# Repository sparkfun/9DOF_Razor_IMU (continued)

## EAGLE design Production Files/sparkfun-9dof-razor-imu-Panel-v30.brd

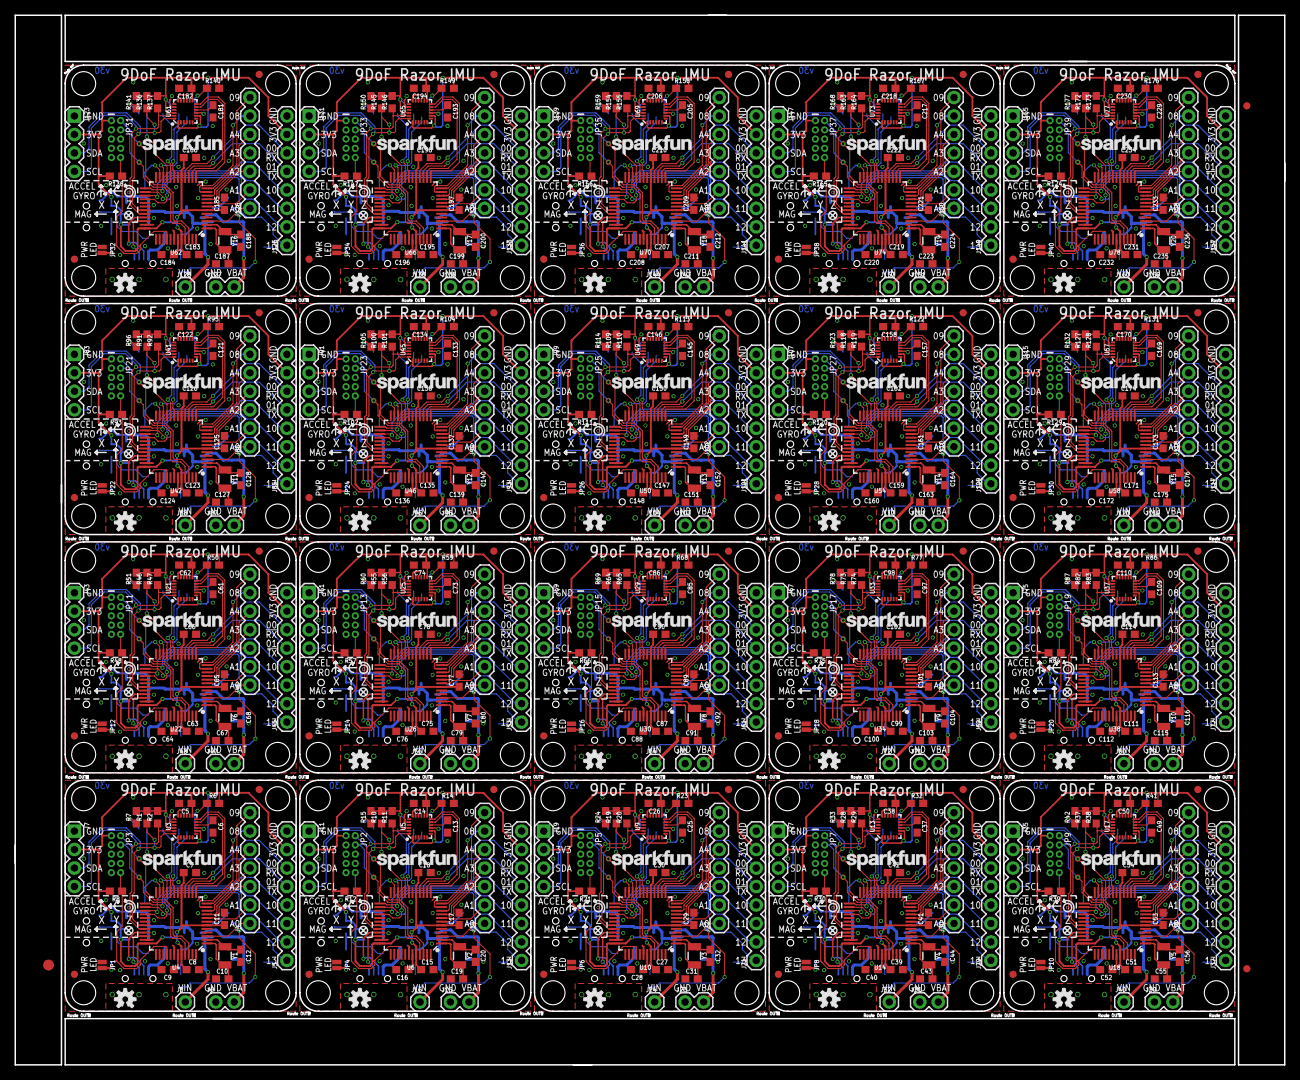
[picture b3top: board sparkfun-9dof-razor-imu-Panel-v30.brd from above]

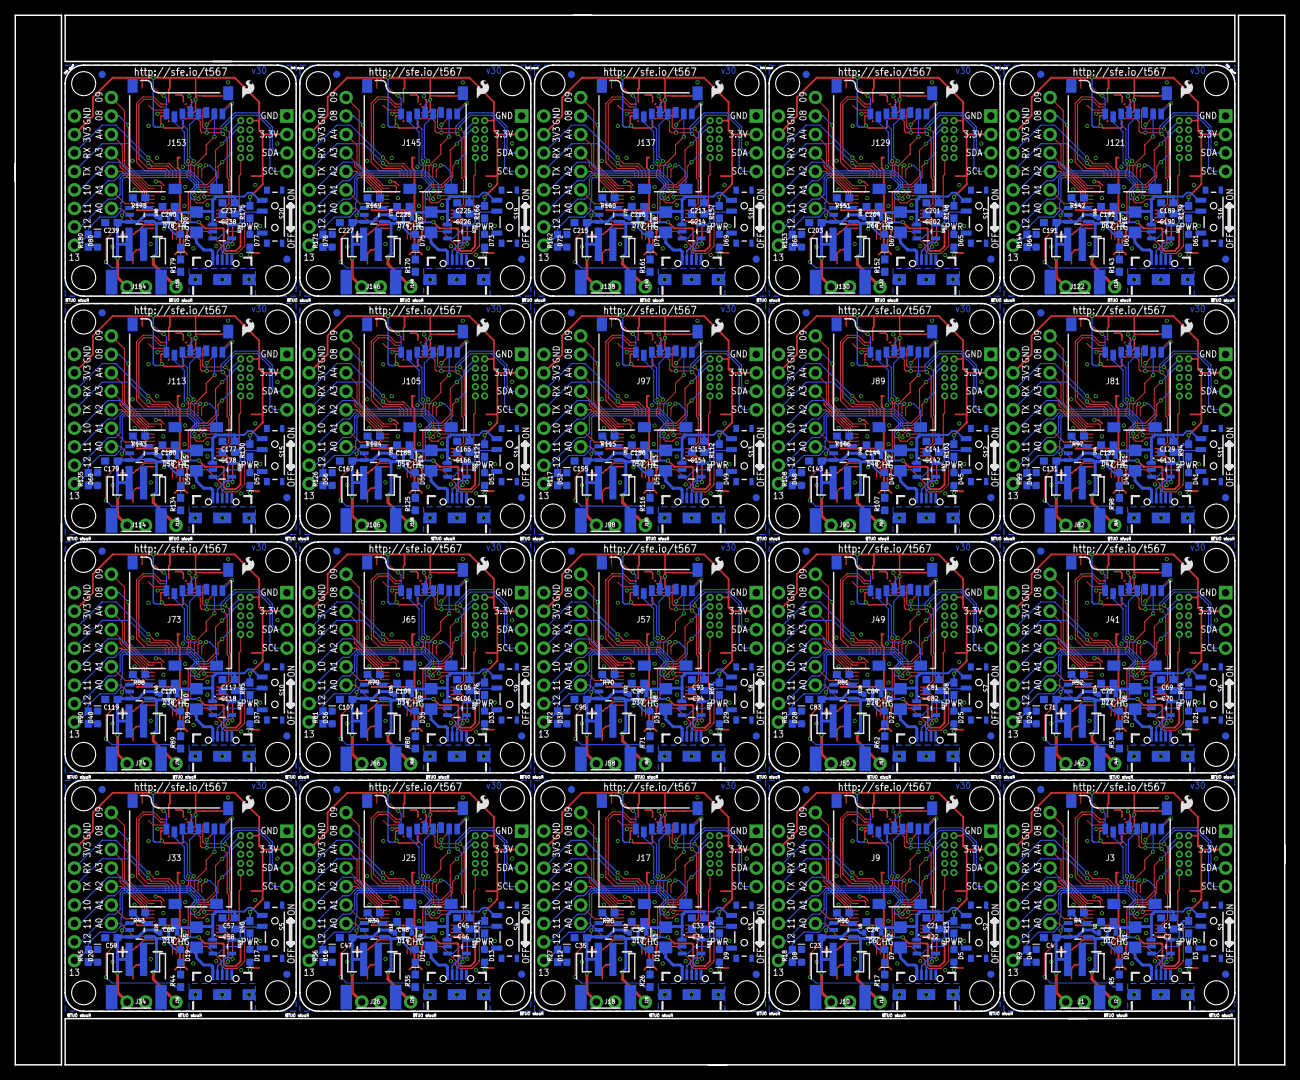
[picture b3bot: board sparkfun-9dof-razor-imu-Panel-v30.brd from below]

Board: 2 copper layers, 174.5 x 144.3 mm, 1103 parts (440 on the bottom side), 920 nets.

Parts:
C1, C21, C33, C45, C57, C69, C81, C93, C105, C117, C129, C141, C153, C165, C177, C189, C201, C213, C225, C237: 1.0uF; 0603
C2, C22, C34, C46, C58, C70, C82, C94, C106, C118, C130, C142, C154, C166, C178, C190, C202, C214, C226, C238: 2.2uF; 0603
C3, C4, C23, C24, C35, C36, C47, C48, C59, C60, C71, C72, C83, C84, C95, C96, C107, C108, C119, C120, C131, C132, C143, C144, C155, C156, C167, C168, C179, C180, C191, C192, C203, C204, C215, C216, C227, C228, C239, C240: 4.7uF; 0603
C5, C6, C7, C8, C9, C11, C13, C14, C15, C16, C17, C18, C25, C26, C27, C28, C29, C30, C37, C38, C39, C40, C41, C42, C49, C50, C51, C52, C53, C54, C61, C62, C63, C64, C65, C66, C73, C74, C75, C76, C77, C78, C85, C86, C87, C88, C89, C90, C97, C98, C99, C100, C101, C102, C109, C110, C111, C112, C113, C114, C121, C122, C123, C124, C125, C126, C133, C134, C135, C136, C137, C138, C145, C146, C147, C148, C149, C150, C157, C158, C159, C160, C161, C162, C169, C170, C171, C172, C173, C174, C181, C182, C183, C184, C185, C186, C193, C194, C195, C196, C197, C198, C205, C206, C207, C208, C209, C210, C217, C218, C219, C220, C221, C222, C229, C230, C231, C232, C233, C234: 0.1uF; 0603
C10, C12, C19, C20, C31, C32, C43, C44, C55, C56, C67, C68, C79, C80, C91, C92, C103, C104, C115, C116, C127, C128, C139, C140, C151, C152, C163, C164, C175, C176, C187, C188, C199, C200, C211, C212, C223, C224, C235, C236: 15pF; 0603
D1, D6, D10, D14, D18, D22, D26, D30, D34, D38, D42, D46, D50, D54, D58, D62, D66, D70, D74, D78: 1A/23V/620mV; SOD-323
D2, D7, D11, D15, D19, D23, D27, D31, D35, D39, D43, D47, D51, D55, D59, D63, D67, D71, D75, D79: Yellow; LED-0603
D3, D5, D9, D13, D17, D21, D25, D29, D33, D37, D41, D45, D49, D53, D57, D61, D65, D69, D73, D77: RED; LED-0603
D4, D8, D12, D16, D20, D24, D28, D32, D36, D40, D44, D48, D52, D56, D60, D64, D68, D72, D76, D80: BLUE; LED-0603
E$1: FIDUCIAL-1.5X3
E$7, E$8: FIDUCIAL-1X2
F1, F2, F3, F4, F5, F6, F7, F8, F9, F10, F11, F12, F13, F14, F15, F16, F17, F18, F19, F20: 6V/0.5A; 1206
FD1, FD2, FD3, FD4, FD5, FD6, FD7, FD8, FD9, FD10, FD11, FD12, FD13, FD14, FD15, FD16, FD17, FD18, FD19, FD20, FD21, FD22, FD23, FD24, FD25, FD26, FD27, FD28, FD29, FD30, FD31, FD32, FD33, FD34, FD35, FD36, FD37, FD38, FD39, FD40, FD41, FD42, FD43, FD44, FD45, FD46, FD47, FD48, FD49, FD50, FD51, FD52, FD53, FD54, FD55, FD56, FD57, FD58, FD59, FD60, FD61, FD62, FD63, FD64, FD65, FD66, FD67, FD68, FD69, FD70, FD71, FD72, FD73, FD74, FD75, FD76, FD77, FD78, FD79, FD80: FIDUCIAL1X2; FIDUCIAL-1X2
H1, H2, H3, H4, H5, H6, H7, H8, H9, H10, H11, H12, H13, H14, H15, H16, H17, H18, H19, H20, H21, H22, H23, H24, H25, H26, H27, H28, H29, H30, H31, H32, H33, H34, H35, H36, H37, H38, H39, H40, H41, H42, H43, H44, H45, H46, H47, H48, H49, H50, H51, H52, H53, H54, H55, H56, H57, H58, H59, H60, H61, H62, H63, H64, H65, H66, H67, H68, H69, H70, H71, H72, H73, H74, H75, H76, H77, H78, H79, H80: STAND-OFF
J1, J10, J18, J26, J34, J42, J50, J58, J66, J74, J82, J90, J98, J106, J114, J122, J130, J138, J146, J154: LiPo; JST-2-SMD
J2, J12, J20, J28, J36, J44, J52, J60, J68, J76, J84, J92, J100, J108, J116, J124, J132, J140, J148, J156: USB-B-MICRO-SMD_V03
J3, J9, J17, J25, J33, J41, J49, J57, J65, J73, J81, J89, J97, J105, J113, J121, J129, J137, J145, J153: USD_CONNECTOR; MICRO-SD-SOCKET-PP
J4, J14, J22, J30, J38, J46, J54, J62, J70, J78, J86, J94, J102, J110, J118, J126, J134, J142, J150, J158: 1X07
J5, J13, J21, J29, J37, J45, J53, J61, J69, J77, J85, J93, J101, J109, J117, J125, J133, J141, J149, J157: 1X08
J6, J15, J23, J31, J39, J47, J55, J63, J71, J79, J87, J95, J103, J111, J119, J127, J135, J143, J151, J159: 1X02
J7, J11, J19, J27, J35, J43, J51, J59, J67, J75, J83, J91, J99, J107, J115, J123, J131, J139, J147, J155: 1X04
J8, J16, J24, J32, J40, J48, J56, J64, J72, J80, J88, J96, J104, J112, J120, J128, J136, J144, J152, J160: 1X01
JP1, JP4, JP6, JP8, JP10, JP12, JP14, JP16, JP18, JP20, JP22, JP24, JP26, JP28, JP30, JP32, JP34, JP36, JP38, JP40: LED; SMT-JUMPER_2_NC_PASTE_NO-SILK
JP2, JP3, JP5, JP7, JP9, JP11, JP13, JP15, JP17, JP19, JP21, JP23, JP25, JP27, JP29, JP31, JP33, JP35, JP37, JP39: CORTEX_DEBUGPTH; 2X5-PTH-1.27MM
LOGO1, LOGO4, LOGO7, LOGO10, LOGO13, LOGO16, LOGO19, LOGO22, LOGO25, LOGO28, LOGO31, LOGO34, LOGO37, LOGO40, LOGO43, LOGO46, LOGO49, LOGO52, LOGO55, LOGO58: SFE_LOGO_FLAME.1_INCH; SFE_LOGO_FLAME_.1
LOGO2, LOGO5, LOGO8, LOGO11, LOGO14, LOGO17, LOGO20, LOGO23, LOGO26, LOGO29, LOGO32, LOGO35, LOGO38, LOGO41, LOGO44, LOGO47, LOGO50, LOGO53, LOGO56, LOGO59: OSHW-LOGOS; OSHW-LOGO-S
LOGO3, LOGO6, LOGO9, LOGO12, LOGO15, LOGO18, LOGO21, LOGO24, LOGO27, LOGO30, LOGO33, LOGO36, LOGO39, LOGO42, LOGO45, LOGO48, LOGO51, LOGO54, LOGO57, LOGO60: SFE_LOGO_NAME.1_INCH; SFE_LOGO_NAME_.1
R1, R2, R10, R11, R19, R20, R28, R29, R37, R38, R46, R47, R55, R56, R64, R65, R73, R74, R82, R83, R91, R92, R100, R101, R109, R110, R118, R119, R127, R128, R136, R137, R145, R146, R154, R155, R163, R164, R172, R173: 4.7k; 0603
R3, R5, R9, R13, R17, R18, R22, R26, R27, R31, R35, R36, R40, R44, R45, R49, R53, R54, R58, R62, R63, R67, R71, R72, R76, R80, R81, R85, R89, R90, R94, R98, R99, R103, R107, R108, R112, R116, R117, R121, R125, R126, R130, R134, R135, R139, R143, R144, R148, R152, R153, R157, R161, R162, R166, R170, R171, R175, R179, R180: 1k; 0603
R4, R16, R25, R34, R43, R52, R61, R70, R79, R88, R97, R106, R115, R124, R133, R142, R151, R160, R169, R178: 2.2k; 0603
R6, R7, R14, R15, R23, R24, R32, R33, R41, R42, R50, R51, R59, R60, R68, R69, R77, R78, R86, R87, R95, R96, R104, R105, R113, R114, R122, R123, R131, R132, R140, R141, R149, R150, R158, R159, R167, R168, R176, R177: 100k; 0603
R8, R12, R21, R30, R39, R48, R57, R66, R75, R84, R93, R102, R111, R120, R129, R138, R147, R156, R165, R174: 10k; 0603
S1, S2, S3, S4, S5, S6, S7, S8, S9, S10, S11, S12, S13, S14, S15, S16, S17, S18, S19, S20: SWITCH-SPST-SMD-A
TP1, TP2, TP3, TP4, TP5, TP6, TP7, TP8, TP9, TP10, TP11, TP12, TP13, TP14, TP15, TP16, TP17, TP18, TP19, TP20, TP21, TP22, TP23, TP24, TP25, TP26, TP27, TP28, TP29, TP30, TP31, TP32, TP33, TP34, TP35, TP36, TP37, TP38, TP39, TP40: TEST-POINT3; PAD.03X.03
U1, U7, U11, U15, U19, U23, U27, U31, U35, U39, U43, U47, U51, U55, U59, U63, U67, U71, U75, U79: 3.3V; SOT23-5
U2, U8, U12, U16, U20, U24, U28, U32, U36, U40, U44, U48, U52, U56, U60, U64, U68, U72, U76, U80: MCP73831; SOT23-5
U3, U5, U9, U13, U17, U21, U25, U29, U33, U37, U41, U45, U49, U53, U57, U61, U65, U69, U73, U77: MPU-9250; QFN24-3X3
U4, U6, U10, U14, U18, U22, U26, U30, U34, U38, U42, U46, U50, U54, U58, U62, U66, U70, U74, U78: ATSAMD21G-A; TQFP-48
Y1, Y2, Y3, Y4, Y5, Y6, Y7, Y8, Y9, Y10, Y11, Y12, Y13, Y14, Y15, Y16, Y17, Y18, Y19, Y20: 32.768kHz; CRYSTAL-SMD-3.2X1.5MM

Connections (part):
3.3V: C2.1, C5.1, C7.1, C8.1, C11.1, J3.VCC, J5.7, J7.2, JP3.1, R1.2, R2.2, R3.2, R6.2, R7.2, R8.2, U1.5, U3.1, U3.8, U3.13, U3.22, U4.6, U4.17, U4.36, U4.44
3.3V1: C14.1, C15.1, C17.1, C18.1, C22.1, J9.VCC, J11.2, J13.7, JP2.1, R10.2, R11.2, R12.2, R13.2, R14.2, R15.2, U5.1, U5.8, U5.13, U5.22, U6.6, U6.17, U6.36, U6.44, U7.5
3.3V2: C26.1, C27.1, C29.1, C30.1, C34.1, J17.VCC, J19.2, J21.7, JP5.1, R19.2, R20.2, R21.2, R22.2, R23.2, R24.2, U9.1, U9.8, U9.13, U9.22, U10.6, U10.17, U10.36, U10.44, U11.5
3.3V3: C38.1, C39.1, C41.1, C42.1, C46.1, J25.VCC, J27.2, J29.7, JP7.1, R28.2, R29.2, R30.2, R31.2, R32.2, R33.2, U13.1, U13.8, U13.13, U13.22, U14.6, U14.17, U14.36, U14.44, U15.5
3.3V4: C50.1, C51.1, C53.1, C54.1, C58.1, J33.VCC, J35.2, J37.7, JP9.1, R37.2, R38.2, R39.2, R40.2, R41.2, R42.2, U17.1, U17.8, U17.13, U17.22, U18.6, U18.17, U18.36, U18.44, U19.5
3.3V5: C62.1, C63.1, C65.1, C66.1, C70.1, J41.VCC, J43.2, J45.7, JP11.1, R46.2, R47.2, R48.2, R49.2, R50.2, R51.2, U21.1, U21.8, U21.13, U21.22, U22.6, U22.17, U22.36, U22.44, U23.5
3.3V6: C74.1, C75.1, C77.1, C78.1, C82.1, J49.VCC, J51.2, J53.7, JP13.1, R55.2, R56.2, R57.2, R58.2, R59.2, R60.2, U25.1, U25.8, U25.13, U25.22, U26.6, U26.17, U26.36, U26.44, U27.5
3.3V7: C86.1, C87.1, C89.1, C90.1, C94.1, J57.VCC, J59.2, J61.7, JP15.1, R64.2, R65.2, R66.2, R67.2, R68.2, R69.2, U29.1, U29.8, U29.13, U29.22, U30.6, U30.17, U30.36, U30.44, U31.5
3.3V8: C98.1, C99.1, C101.1, C102.1, C106.1, J65.VCC, J67.2, J69.7, JP17.1, R73.2, R74.2, R75.2, R76.2, R77.2, R78.2, U33.1, U33.8, U33.13, U33.22, U34.6, U34.17, U34.36, U34.44, U35.5
3.3V9: C110.1, C111.1, C113.1, C114.1, C118.1, J73.VCC, J75.2, J77.7, JP19.1, R82.2, R83.2, R84.2, R85.2, R86.2, R87.2, U37.1, U37.8, U37.13, U37.22, U38.6, U38.17, U38.36, U38.44, U39.5
3.3V10: C122.1, C123.1, C125.1, C126.1, C130.1, J81.VCC, J83.2, J85.7, JP21.1, R91.2, R92.2, R93.2, R94.2, R95.2, R96.2, U41.1, U41.8, U41.13, U41.22, U42.6, U42.17, U42.36, U42.44, U43.5
3.3V11: C134.1, C135.1, C137.1, C138.1, C142.1, J89.VCC, J91.2, J93.7, JP23.1, R100.2, R101.2, R102.2, R103.2, R104.2, R105.2, U45.1, U45.8, U45.13, U45.22, U46.6, U46.17, U46.36, U46.44, U47.5
3.3V12: C146.1, C147.1, C149.1, C150.1, C154.1, J97.VCC, J99.2, J101.7, JP25.1, R109.2, R110.2, R111.2, R112.2, R113.2, R114.2, U49.1, U49.8, U49.13, U49.22, U50.6, U50.17, U50.36, U50.44, U51.5
3.3V13: C158.1, C159.1, C161.1, C162.1, C166.1, J105.VCC, J107.2, J109.7, JP27.1, R118.2, R119.2, R120.2, R121.2, R122.2, R123.2, U53.1, U53.8, U53.13, U53.22, U54.6, U54.17, U54.36, U54.44, U55.5
3.3V14: C170.1, C171.1, C173.1, C174.1, C178.1, J113.VCC, J115.2, J117.7, JP29.1, R127.2, R128.2, R129.2, R130.2, R131.2, R132.2, U57.1, U57.8, U57.13, U57.22, U58.6, U58.17, U58.36, U58.44, U59.5
3.3V15: C182.1, C183.1, C185.1, C186.1, C190.1, J121.VCC, J123.2, J125.7, JP31.1, R136.2, R137.2, R138.2, R139.2, R140.2, R141.2, U61.1, U61.8, U61.13, U61.22, U62.6, U62.17, U62.36, U62.44, U63.5
3.3V16: C194.1, C195.1, C197.1, C198.1, C202.1, J129.VCC, J131.2, J133.7, JP33.1, R145.2, R146.2, R147.2, R148.2, R149.2, R150.2, U65.1, U65.8, U65.13, U65.22, U66.6, U66.17, U66.36, U66.44, U67.5
3.3V17: C206.1, C207.1, C209.1, C210.1, C214.1, J137.VCC, J139.2, J141.7, JP35.1, R154.2, R155.2, R156.2, R157.2, R158.2, R159.2, U69.1, U69.8, U69.13, U69.22, U70.6, U70.17, U70.36, U70.44, U71.5
3.3V18: C218.1, C219.1, C221.1, C222.1, C226.1, J145.VCC, J147.2, J149.7, JP37.1, R163.2, R164.2, R165.2, R166.2, R167.2, R168.2, U73.1, U73.8, U73.13, U73.22, U74.6, U74.17, U74.36, U74.44, U75.5
3.3V19: C230.1, C231.1, C233.1, C234.1, C238.1, J153.VCC, J155.2, J157.7, JP39.1, R172.2, R173.2, R174.2, R175.2, R176.2, R177.2, U77.1, U77.8, U77.13, U77.22, U78.6, U78.17, U78.36, U78.44, U79.5
!RESET: JP3.10, R8.1, U4.40
!RESET1: JP2.10, R12.1, U6.40
!RESET2: JP5.10, R21.1, U10.40
!RESET3: JP7.10, R30.1, U14.40
!RESET4: JP9.10, R39.1, U18.40
!RESET5: JP11.10, R48.1, U22.40
!RESET6: JP13.10, R57.1, U26.40
!RESET7: JP15.10, R66.1, U30.40
!RESET8: JP17.10, R75.1, U34.40
!RESET9: JP19.10, R84.1, U38.40
!RESET10: JP21.10, R93.1, U42.40
!RESET11: JP23.10, R102.1, U46.40
!RESET12: JP25.10, R111.1, U50.40
!RESET13: JP27.10, R120.1, U54.40
!RESET14: JP29.10, R129.1, U58.40
!RESET15: JP31.10, R138.1, U62.40
!RESET16: JP33.10, R147.1, U66.40
!RESET17: JP35.10, R156.1, U70.40
!RESET18: JP37.10, R165.1, U74.40
!RESET19: JP39.10, R174.1, U78.40
A0: J4.1, U4.3
A1: J4.2, U4.7
A2: J4.3, U4.8
A3: J4.4, U4.9
A4: J4.5, U4.10
A6: J14.2, U6.7
A7: J14.1, U6.3
A8: J14.3, U6.8
A9: J14.4, U6.9
A10: J14.5, U6.10
A12: J22.2, U10.7
A13: J22.1, U10.3
A14: J22.3, U10.8
A15: J22.4, U10.9
A16: J22.5, U10.10
A18: J30.2, U14.7
A19: J30.1, U14.3
A20: J30.3, U14.8
A21: J30.4, U14.9
A22: J30.5, U14.10
A24: J38.2, U18.7
A25: J38.1, U18.3
A26: J38.3, U18.8
A27: J38.4, U18.9
A28: J38.5, U18.10
A30: J46.2, U22.7
A31: J46.1, U22.3
A32: J46.3, U22.8
A33: J46.4, U22.9
A34: J46.5, U22.10
A36: J54.2, U26.7
A37: J54.1, U26.3
A38: J54.3, U26.8
A39: J54.4, U26.9
A40: J54.5, U26.10
A42: J62.2, U30.7
A43: J62.1, U30.3
A44: J62.3, U30.8
A45: J62.4, U30.9
A46: J62.5, U30.10
A48: J70.2, U34.7
A49: J70.1, U34.3
A50: J70.3, U34.8
A51: J70.4, U34.9
A52: J70.5, U34.10
A54: J78.2, U38.7
A55: J78.1, U38.3
A56: J78.3, U38.8
A57: J78.4, U38.9
A58: J78.5, U38.10
A60: J86.2, U42.7
A61: J86.1, U42.3
A62: J86.3, U42.8
A63: J86.4, U42.9
A64: J86.5, U42.10
A66: J94.2, U46.7
A67: J94.1, U46.3
A68: J94.3, U46.8
A69: J94.4, U46.9
A70: J94.5, U46.10
A72: J102.2, U50.7
A73: J102.1, U50.3
A74: J102.3, U50.8
A75: J102.4, U50.9
A76: J102.5, U50.10
A78: J110.2, U54.7
A79: J110.1, U54.3
A80: J110.3, U54.8
A81: J110.4, U54.9
A82: J110.5, U54.10
A84: J118.2, U58.7
A85: J118.1, U58.3
A86: J118.3, U58.8
A87: J118.4, U58.9
A88: J118.5, U58.10
A90: J126.2, U62.7
A91: J126.1, U62.3
A92: J126.3, U62.8
A93: J126.4, U62.9
A94: J126.5, U62.10
A96: J134.2, U66.7
A97: J134.1, U66.3
A98: J134.3, U66.8
A99: J134.4, U66.9
A100: J134.5, U66.10
A102: J142.2, U70.7
A103: J142.1, U70.3
A104: J142.3, U70.8
A105: J142.4, U70.9
A106: J142.5, U70.10
A108: J150.2, U74.7
A109: J150.1, U74.3
A110: J150.3, U74.8
A111: J150.4, U74.9
A112: J150.5, U74.10
A114: J158.2, U78.7
A115: J158.1, U78.3
A116: J158.3, U78.8
A117: J158.4, U78.9
A118: J158.5, U78.10
CHG_LED: R5.1, U2.1
CHG_LED1: R17.1, U8.1
CHG_LED2: R26.1, U12.1
CHG_LED3: R35.1, U16.1
CHG_LED4: R44.1, U20.1
CHG_LED5: R53.1, U24.1
CHG_LED6: R62.1, U28.1
CHG_LED7: R71.1, U32.1
CHG_LED8: R80.1, U36.1
CHG_LED9: R89.1, U40.1
CHG_LED10: R98.1, U44.1
CHG_LED11: R107.1, U48.1
CHG_LED12: R116.1, U52.1
CHG_LED13: R125.1, U56.1
CHG_LED14: R134.1, U60.1
CHG_LED15: R143.1, U64.1
CHG_LED16: R152.1, U68.1
CHG_LED17: R161.1, U72.1
CHG_LED18: R170.1, U76.1
CHG_LED19: R179.1, U80.1
D0/RXI: J5.6, U4.16
D0/RXI1: J13.6, U6.16
D0/RXI2: J21.6, U10.16
D0/RXI3: J29.6, U14.16
D0/RXI4: J37.6, U18.16
D0/RXI5: J45.6, U22.16
D0/RXI6: J53.6, U26.16
D0/RXI7: J61.6, U30.16
D0/RXI8: J69.6, U34.16
D0/RXI9: J77.6, U38.16
D0/RXI10: J85.6, U42.16
D0/RXI11: J93.6, U46.16
D0/RXI12: J101.6, U50.16
D0/RXI13: J109.6, U54.16
D0/RXI14: J117.6, U58.16
D0/RXI15: J125.6, U62.16
D0/RXI16: J133.6, U66.16
D0/RXI17: J141.6, U70.16
D0/RXI18: J149.6, U74.16
D0/RXI19: J157.6, U78.16
D1/TXO: J5.5, U4.15
D1/TXO1: J13.5, U6.15
D1/TXO2: J21.5, U10.15
D1/TXO3: J29.5, U14.15
D1/TXO4: J37.5, U18.15
D1/TXO5: J45.5, U22.15
D1/TXO6: J53.5, U26.15
D1/TXO7: J61.5, U30.15
D1/TXO8: J69.5, U34.15
D1/TXO9: J77.5, U38.15
D1/TXO10: J85.5, U42.15
D1/TXO11: J93.5, U46.15
D1/TXO12: J101.5, U50.15
D1/TXO13: J109.5, U54.15
D1/TXO14: J117.5, U58.15
D1/TXO15: J125.5, U62.15
D1/TXO16: J133.5, U66.15
D1/TXO17: J141.5, U70.15
D1/TXO18: J149.5, U74.15
D1/TXO19: J157.5, U78.15
D2/SD_CD: J3.CD1, U4.23
D2/SD_CD1: J9.CD1, U6.23
D2/SD_CD2: J17.CD1, U10.23
D2/SD_CD3: J25.CD1, U14.23
D2/SD_CD4: J33.CD1, U18.23
D2/SD_CD5: J41.CD1, U22.23
D2/SD_CD6: J49.CD1, U26.23
D2/SD_CD7: J57.CD1, U30.23
D2/SD_CD8: J65.CD1, U34.23
D2/SD_CD9: J73.CD1, U38.23
D2/SD_CD10: J81.CD1, U42.23
D2/SD_CD11: J89.CD1, U46.23
D2/SD_CD12: J97.CD1, U50.23
D2/SD_CD13: J105.CD1, U54.23
D2/SD_CD14: J113.CD1, U58.23
D2/SD_CD15: J121.CD1, U62.23
D2/SD_CD16: J129.CD1, U66.23
D2/SD_CD17: J137.CD1, U70.23
D2/SD_CD18: J145.CD1, U74.23
D2/SD_CD19: J153.CD1, U78.23
D3/FSYNC: U3.11, U4.14
D3/FSYNC1: U5.11, U6.14
D3/FSYNC2: U9.11, U10.14
D3/FSYNC3: U13.11, U14.14
D3/FSYNC4: U17.11, U18.14
D3/FSYNC5: U21.11, U22.14
D3/FSYNC6: U25.11, U26.14
D3/FSYNC7: U29.11, U30.14
D3/FSYNC8: U33.11, U34.14
D3/FSYNC9: U37.11, U38.14
D3/FSYNC10: U41.11, U42.14
D3/FSYNC11: U45.11, U46.14
D3/FSYNC12: U49.11, U50.14
D3/FSYNC13: U53.11, U54.14
D3/FSYNC14: U57.11, U58.14
D3/FSYNC15: U61.11, U62.14
D3/FSYNC16: U65.11, U66.14
D3/FSYNC17: U69.11, U70.14
D3/FSYNC18: U73.11, U74.14
D3/FSYNC19: U77.11, U78.14
D4: J13.2, U6.28
D4/INT: U3.12, U4.13
D4/INT1: U5.12, U6.13
D4/INT2: U9.12, U10.13
D4/INT3: U13.12, U14.13
D4/INT4: U17.12, U18.13
D4/INT5: U21.12, U22.13
D4/INT6: U25.12, U26.13
D4/INT7: U29.12, U30.13
D4/INT8: U33.12, U34.13
D4/INT9: U37.12, U38.13
D4/INT10: U41.12, U42.13
D4/INT11: U45.12, U46.13
D4/INT12: U49.12, U50.13
D4/INT13: U53.12, U54.13
D4/INT14: U57.12, U58.13
D4/INT15: U61.12, U62.13
D4/INT16: U65.12, U66.13
D4/INT17: U69.12, U70.13
D4/INT18: U73.12, U74.13
D4/INT19: U77.12, U78.13
D8: J4.6, U4.11
D9: J4.7, U4.12
D10: J5.4, U4.27
D11: J5.3, U4.25
D12: J5.2, U4.28
D13: J5.1, R9.2, U4.26
D14: J13.4, U6.27
D15: J13.3, U6.25
D16: J13.1, R18.2, U6.26
D17: J14.6, U6.11
D18: J14.7, U6.12
D22: J21.2, U10.28
D23: J21.4, U10.27
D24: J21.3, U10.25
D25: J21.1, R27.2, U10.26
D26: J22.6, U10.11
D27: J22.7, U10.12
D31: J29.2, U14.28
D32: J29.4, U14.27
D33: J29.3, U14.25
D34: J29.1, R36.2, U14.26
D35: J30.6, U14.11
D36: J30.7, U14.12
D40: J37.2, U18.28
D41: J37.4, U18.27
D42: J37.3, U18.25
D43: J37.1, R45.2, U18.26
D44: J38.6, U18.11
D45: J38.7, U18.12
D49: J45.2, U22.28
D50: J45.4, U22.27
D51: J45.3, U22.25
D52: J45.1, R54.2, U22.26
D53: J46.6, U22.11
D54: J46.7, U22.12
D58: J53.2, U26.28
D59: J53.4, U26.27
D60: J53.3, U26.25
D61: J53.1, R63.2, U26.26
D62: J54.6, U26.11
D63: J54.7, U26.12
D67: J61.2, U30.28
D68: J61.4, U30.27
D69: J61.3, U30.25
D70: J61.1, R72.2, U30.26
D71: J62.6, U30.11
D72: J62.7, U30.12
D76: J69.2, U34.28
D77: J69.4, U34.27
D78: J69.3, U34.25
D79: J69.1, R81.2, U34.26
D80: J70.6, U34.11
D81: J70.7, U34.12
D85: J77.2, U38.28
D86: J77.4, U38.27
D87: J77.3, U38.25
D88: J77.1, R90.2, U38.26
D89: J78.6, U38.11
D90: J78.7, U38.12
D94: J85.2, U42.28
D95: J85.4, U42.27
D96: J85.3, U42.25
D97: J85.1, R99.2, U42.26
D98: J86.6, U42.11
D99: J86.7, U42.12
D103: J93.2, U46.28
D104: J93.4, U46.27
D105: J93.3, U46.25
D106: J93.1, R108.2, U46.26
D107: J94.6, U46.11
D108: J94.7, U46.12
D112: J101.2, U50.28
D113: J101.4, U50.27
D114: J101.3, U50.25
D115: J101.1, R117.2, U50.26
D116: J102.6, U50.11
D117: J102.7, U50.12
D121: J109.2, U54.28
D122: J109.4, U54.27
D123: J109.3, U54.25
D124: J109.1, R126.2, U54.26
D125: J110.6, U54.11
D126: J110.7, U54.12
D130: J117.2, U58.28
D131: J117.4, U58.27
D132: J117.3, U58.25
D133: J117.1, R135.2, U58.26
D134: J118.6, U58.11
D135: J118.7, U58.12
D139: J125.2, U62.28
D140: J125.4, U62.27
D141: J125.3, U62.25
D142: J125.1, R144.2, U62.26
D143: J126.6, U62.11
D144: J126.7, U62.12
D148: J133.2, U66.28
D149: J133.4, U66.27
D150: J133.3, U66.25
D151: J133.1, R153.2, U66.26
D152: J134.6, U66.11
D153: J134.7, U66.12
D157: J141.2, U70.28
D158: J141.4, U70.27
D159: J141.3, U70.25
D160: J141.1, R162.2, U70.26
D161: J142.6, U70.11
D162: J142.7, U70.12
D166: J149.2, U74.28
D167: J149.4, U74.27
D168: J149.3, U74.25
D169: J149.1, R171.2, U74.26
D170: J150.6, U74.11
D171: J150.7, U74.12
D175: J157.2, U78.28
D176: J157.4, U78.27
D177: J157.3, U78.25
D178: J157.1, R180.2, U78.26
D179: J158.6, U78.11
D180: J158.7, U78.12
D+: J2.D+, U4.34
D+1: J12.D+, U6.34
D+2: J20.D+, U10.34
D+3: J28.D+, U14.34
D+4: J36.D+, U18.34
D+5: J44.D+, U22.34
D+6: J52.D+, U26.34
D+7: J60.D+, U30.34
D+8: J68.D+, U34.34
D+9: J76.D+, U38.34
D+10: J84.D+, U42.34
D+11: J92.D+, U46.34
D+12: J100.D+, U50.34
D+13: J108.D+, U54.34
D+14: J116.D+, U58.34
D+15: J124.D+, U62.34
D+16: J132.D+, U66.34
D+17: J140.D+, U70.34
D+18: J148.D+, U74.34
D+19: J156.D+, U78.34
D-: J2.D-, U4.33
D-1: J12.D-, U6.33
D-2: J20.D-, U10.33
D-3: J28.D-, U14.33
D-4: J36.D-, U18.33
D-5: J44.D-, U22.33
D-6: J52.D-, U26.33
D-7: J60.D-, U30.33
D-8: J68.D-, U34.33
D-9: J76.D-, U38.33
D-10: J84.D-, U42.33
D-11: J92.D-, U46.33
D-12: J100.D-, U50.33
D-13: J108.D-, U54.33
D-14: J116.D-, U58.33
D-15: J124.D-, U62.33
D-16: J132.D-, U66.33
D-17: J140.D-, U70.33
D-18: J148.D-, U74.33
D-19: J156.D-, U78.33
GND: C1.2, C2.2, C3.2, C4.2, C5.2, C6.2, C7.2, C8.2, C9.2, C10.1, C11.2, C12.2, D4.C, J1.1, J2.GND, J3.GND, J3.GND1, J3.GND3, J5.8, J6.1, J7.1, JP1.1, JP3.3, JP3.5, R4.1, S1.3, U1.2, U2.2, U3.9, U3.18, U3.20, U4.5, U4.18, U4.35, U4.42
GND1: C13.2, C14.2, C15.2, C16.2, C17.2, C18.2, C19.1, C20.2, C21.2, C22.2, C23.2, C24.2, D8.C, J9.GND, J9.GND1, J9.GND3, J10.1, J11.1, J12.GND, J13.8, J15.1, JP2.3, JP2.5, JP4.1, R16.1, S2.3, U5.9, U5.18, U5.20, U6.5, U6.18, U6.35, U6.42, U7.2, U8.2
GND2: C25.2, C26.2, C27.2, C28.2, C29.2, C30.2, C31.1, C32.2, C33.2, C34.2, C35.2, C36.2, D12.C, J17.GND, J17.GND1, J17.GND3, J18.1, J19.1, J20.GND, J21.8, J23.1, JP5.3, JP5.5, JP6.1, R25.1, S3.3, U9.9, U9.18, U9.20, U10.5, U10.18, U10.35, U10.42, U11.2, U12.2
GND3: C37.2, C38.2, C39.2, C40.2, C41.2, C42.2, C43.1, C44.2, C45.2, C46.2, C47.2, C48.2, D16.C, J25.GND, J25.GND1, J25.GND3, J26.1, J27.1, J28.GND, J29.8, J31.1, JP7.3, JP7.5, JP8.1, R34.1, S4.3, U13.9, U13.18, U13.20, U14.5, U14.18, U14.35, U14.42, U15.2, U16.2
GND4: C49.2, C50.2, C51.2, C52.2, C53.2, C54.2, C55.1, C56.2, C57.2, C58.2, C59.2, C60.2, D20.C, J33.GND, J33.GND1, J33.GND3, J34.1, J35.1, J36.GND, J37.8, J39.1, JP9.3, JP9.5, JP10.1, R43.1, S5.3, U17.9, U17.18, U17.20, U18.5, U18.18, U18.35, U18.42, U19.2, U20.2
GND5: C61.2, C62.2, C63.2, C64.2, C65.2, C66.2, C67.1, C68.2, C69.2, C70.2, C71.2, C72.2, D24.C, J41.GND, J41.GND1, J41.GND3, J42.1, J43.1, J44.GND, J45.8, J47.1, JP11.3, JP11.5, JP12.1, R52.1, S6.3, U21.9, U21.18, U21.20, U22.5, U22.18, U22.35, U22.42, U23.2, U24.2
GND6: C73.2, C74.2, C75.2, C76.2, C77.2, C78.2, C79.1, C80.2, C81.2, C82.2, C83.2, C84.2, D28.C, J49.GND, J49.GND1, J49.GND3, J50.1, J51.1, J52.GND, J53.8, J55.1, JP13.3, JP13.5, JP14.1, R61.1, S7.3, U25.9, U25.18, U25.20, U26.5, U26.18, U26.35, U26.42, U27.2, U28.2
GND7: C85.2, C86.2, C87.2, C88.2, C89.2, C90.2, C91.1, C92.2, C93.2, C94.2, C95.2, C96.2, D32.C, J57.GND, J57.GND1, J57.GND3, J58.1, J59.1, J60.GND, J61.8, J63.1, JP15.3, JP15.5, JP16.1, R70.1, S8.3, U29.9, U29.18, U29.20, U30.5, U30.18, U30.35, U30.42, U31.2, U32.2
GND8: C97.2, C98.2, C99.2, C100.2, C101.2, C102.2, C103.1, C104.2, C105.2, C106.2, C107.2, C108.2, D36.C, J65.GND, J65.GND1, J65.GND3, J66.1, J67.1, J68.GND, J69.8, J71.1, JP17.3, JP17.5, JP18.1, R79.1, S9.3, U33.9, U33.18, U33.20, U34.5, U34.18, U34.35, U34.42, U35.2, U36.2
GND9: C109.2, C110.2, C111.2, C112.2, C113.2, C114.2, C115.1, C116.2, C117.2, C118.2, C119.2, C120.2, D40.C, J73.GND, J73.GND1, J73.GND3, J74.1, J75.1, J76.GND, J77.8, J79.1, JP19.3, JP19.5, JP20.1, R88.1, S10.3, U37.9, U37.18, U37.20, U38.5, U38.18, U38.35, U38.42, U39.2, U40.2
GND10: C121.2, C122.2, C123.2, C124.2, C125.2, C126.2, C127.1, C128.2, C129.2, C130.2, C131.2, C132.2, D44.C, J81.GND, J81.GND1, J81.GND3, J82.1, J83.1, J84.GND, J85.8, J87.1, JP21.3, JP21.5, JP22.1, R97.1, S11.3, U41.9, U41.18, U41.20, U42.5, U42.18, U42.35, U42.42, U43.2, U44.2
GND11: C133.2, C134.2, C135.2, C136.2, C137.2, C138.2, C139.1, C140.2, C141.2, C142.2, C143.2, C144.2, D48.C, J89.GND, J89.GND1, J89.GND3, J90.1, J91.1, J92.GND, J93.8, J95.1, JP23.3, JP23.5, JP24.1, R106.1, S12.3, U45.9, U45.18, U45.20, U46.5, U46.18, U46.35, U46.42, U47.2, U48.2
GND12: C145.2, C146.2, C147.2, C148.2, C149.2, C150.2, C151.1, C152.2, C153.2, C154.2, C155.2, C156.2, D52.C, J97.GND, J97.GND1, J97.GND3, J98.1, J99.1, J100.GND, J101.8, J103.1, JP25.3, JP25.5, JP26.1, R115.1, S13.3, U49.9, U49.18, U49.20, U50.5, U50.18, U50.35, U50.42, U51.2, U52.2
GND13: C157.2, C158.2, C159.2, C160.2, C161.2, C162.2, C163.1, C164.2, C165.2, C166.2, C167.2, C168.2, D56.C, J105.GND, J105.GND1, J105.GND3, J106.1, J107.1, J108.GND, J109.8, J111.1, JP27.3, JP27.5, JP28.1, R124.1, S14.3, U53.9, U53.18, U53.20, U54.5, U54.18, U54.35, U54.42, U55.2, U56.2
GND14: C169.2, C170.2, C171.2, C172.2, C173.2, C174.2, C175.1, C176.2, C177.2, C178.2, C179.2, C180.2, D60.C, J113.GND, J113.GND1, J113.GND3, J114.1, J115.1, J116.GND, J117.8, J119.1, JP29.3, JP29.5, JP30.1, R133.1, S15.3, U57.9, U57.18, U57.20, U58.5, U58.18, U58.35, U58.42, U59.2, U60.2
GND15: C181.2, C182.2, C183.2, C184.2, C185.2, C186.2, C187.1, C188.2, C189.2, C190.2, C191.2, C192.2, D64.C, J121.GND, J121.GND1, J121.GND3, J122.1, J123.1, J124.GND, J125.8, J127.1, JP31.3, JP31.5, JP32.1, R142.1, S16.3, U61.9, U61.18, U61.20, U62.5, U62.18, U62.35, U62.42, U63.2, U64.2
GND16: C193.2, C194.2, C195.2, C196.2, C197.2, C198.2, C199.1, C200.2, C201.2, C202.2, C203.2, C204.2, D68.C, J129.GND, J129.GND1, J129.GND3, J130.1, J131.1, J132.GND, J133.8, J135.1, JP33.3, JP33.5, JP34.1, R151.1, S17.3, U65.9, U65.18, U65.20, U66.5, U66.18, U66.35, U66.42, U67.2, U68.2
GND17: C205.2, C206.2, C207.2, C208.2, C209.2, C210.2, C211.1, C212.2, C213.2, C214.2, C215.2, C216.2, D72.C, J137.GND, J137.GND1, J137.GND3, J138.1, J139.1, J140.GND, J141.8, J143.1, JP35.3, JP35.5, JP36.1, R160.1, S18.3, U69.9, U69.18, U69.20, U70.5, U70.18, U70.35, U70.42, U71.2, U72.2
GND18: C217.2, C218.2, C219.2, C220.2, C221.2, C222.2, C223.1, C224.2, C225.2, C226.2, C227.2, C228.2, D76.C, J145.GND, J145.GND1, J145.GND3, J146.1, J147.1, J148.GND, J149.8, J151.1, JP37.3, JP37.5, JP38.1, R169.1, S19.3, U73.9, U73.18, U73.20, U74.5, U74.18, U74.35, U74.42, U75.2, U76.2
GND19: C229.2, C230.2, C231.2, C232.2, C233.2, C234.2, C235.1, C236.2, C237.2, C238.2, C239.2, C240.2, D80.C, J153.GND, J153.GND1, J153.GND3, J154.1, J155.1, J156.GND, J157.8, J159.1, JP39.3, JP39.5, JP40.1, R178.1, S20.3, U77.9, U77.18, U77.20, U78.5, U78.18, U78.35, U78.42, U79.2, U80.2
unnamed: F1.1, J2.VBUS
unnamed: C10.2, U4.1, Y1.P$2
unnamed: D4.A, R9.1
unnamed: C12.1, U4.2, Y1.P$1
unnamed: D3.A, R3.1
unnamed: C19.2, U6.1, Y2.P$2
unnamed: R4.2, U2.5
unnamed: J3.RSV1, R6.1
unnamed: J3.RSV2, R7.1
unnamed: C20.1, U6.2, Y2.P$1
unnamed: D2.C, R5.2
unnamed: D3.C, JP1.2
unnamed: D5.A, R13.1
unnamed: F2.1, J12.VBUS
unnamed: J9.RSV1, R14.1
unnamed: J9.RSV2, R15.1
unnamed: R16.2, U8.5
unnamed: D8.A, R18.1
unnamed: D7.C, R17.2
unnamed: D5.C, JP4.2
unnamed: C31.2, U10.1, Y3.P$2
unnamed: C32.1, U10.2, Y3.P$1
unnamed: D9.A, R22.1
unnamed: F3.1, J20.VBUS
unnamed: J17.RSV1, R23.1
unnamed: J17.RSV2, R24.1
unnamed: R25.2, U12.5
unnamed: D12.A, R27.1
unnamed: D11.C, R26.2
unnamed: D9.C, JP6.2
unnamed: C43.2, U14.1, Y4.P$2
unnamed: C44.1, U14.2, Y4.P$1
unnamed: D13.A, R31.1
unnamed: F4.1, J28.VBUS
unnamed: J25.RSV1, R32.1
unnamed: J25.RSV2, R33.1
unnamed: R34.2, U16.5
unnamed: D16.A, R36.1
unnamed: D15.C, R35.2
unnamed: D13.C, JP8.2
unnamed: C55.2, U18.1, Y5.P$2
unnamed: C56.1, U18.2, Y5.P$1
unnamed: D17.A, R40.1
unnamed: F5.1, J36.VBUS
unnamed: J33.RSV1, R41.1
unnamed: J33.RSV2, R42.1
unnamed: R43.2, U20.5
unnamed: D20.A, R45.1
unnamed: D19.C, R44.2
unnamed: D17.C, JP10.2
unnamed: C67.2, U22.1, Y6.P$2
unnamed: C68.1, U22.2, Y6.P$1
unnamed: D21.A, R49.1
unnamed: F6.1, J44.VBUS
unnamed: J41.RSV1, R50.1
unnamed: J41.RSV2, R51.1
unnamed: R52.2, U24.5
unnamed: D24.A, R54.1
unnamed: D23.C, R53.2
unnamed: D21.C, JP12.2
unnamed: C79.2, U26.1, Y7.P$2
unnamed: C80.1, U26.2, Y7.P$1
unnamed: D25.A, R58.1
unnamed: F7.1, J52.VBUS
unnamed: J49.RSV1, R59.1
unnamed: J49.RSV2, R60.1
unnamed: R61.2, U28.5
unnamed: D28.A, R63.1
unnamed: D27.C, R62.2
unnamed: D25.C, JP14.2
unnamed: C91.2, U30.1, Y8.P$2
unnamed: C92.1, U30.2, Y8.P$1
unnamed: D29.A, R67.1
unnamed: F8.1, J60.VBUS
unnamed: J57.RSV1, R68.1
unnamed: J57.RSV2, R69.1
unnamed: R70.2, U32.5
unnamed: D32.A, R72.1
unnamed: D31.C, R71.2
unnamed: D29.C, JP16.2
unnamed: C103.2, U34.1, Y9.P$2
unnamed: C104.1, U34.2, Y9.P$1
unnamed: D33.A, R76.1
unnamed: F9.1, J68.VBUS
unnamed: J65.RSV1, R77.1
unnamed: J65.RSV2, R78.1
unnamed: R79.2, U36.5
unnamed: D36.A, R81.1
unnamed: D35.C, R80.2
unnamed: D33.C, JP18.2
unnamed: C115.2, U38.1, Y10.P$2
unnamed: C116.1, U38.2, Y10.P$1
unnamed: D37.A, R85.1
unnamed: F10.1, J76.VBUS
unnamed: J73.RSV1, R86.1
unnamed: J73.RSV2, R87.1
unnamed: R88.2, U40.5
unnamed: D40.A, R90.1
unnamed: D39.C, R89.2
unnamed: D37.C, JP20.2
unnamed: C127.2, U42.1, Y11.P$2
unnamed: C128.1, U42.2, Y11.P$1
unnamed: D41.A, R94.1
unnamed: F11.1, J84.VBUS
unnamed: J81.RSV1, R95.1
unnamed: J81.RSV2, R96.1
unnamed: R97.2, U44.5
unnamed: D44.A, R99.1
unnamed: D43.C, R98.2
unnamed: D41.C, JP22.2
unnamed: C139.2, U46.1, Y12.P$2
unnamed: C140.1, U46.2, Y12.P$1
unnamed: D45.A, R103.1
unnamed: F12.1, J92.VBUS
unnamed: J89.RSV1, R104.1
unnamed: J89.RSV2, R105.1
unnamed: R106.2, U48.5
unnamed: D48.A, R108.1
unnamed: D47.C, R107.2
unnamed: D45.C, JP24.2
unnamed: C151.2, U50.1, Y13.P$2
unnamed: C152.1, U50.2, Y13.P$1
unnamed: D49.A, R112.1
unnamed: F13.1, J100.VBUS
unnamed: J97.RSV1, R113.1
unnamed: J97.RSV2, R114.1
unnamed: R115.2, U52.5
unnamed: D52.A, R117.1
unnamed: D51.C, R116.2
unnamed: D49.C, JP26.2
unnamed: C163.2, U54.1, Y14.P$2
unnamed: C164.1, U54.2, Y14.P$1
unnamed: D53.A, R121.1
unnamed: F14.1, J108.VBUS
unnamed: J105.RSV1, R122.1
unnamed: J105.RSV2, R123.1
unnamed: R124.2, U56.5
unnamed: D56.A, R126.1
unnamed: D55.C, R125.2
unnamed: D53.C, JP28.2
unnamed: C175.2, U58.1, Y15.P$2
unnamed: C176.1, U58.2, Y15.P$1
unnamed: D57.A, R130.1
unnamed: F15.1, J116.VBUS
unnamed: J113.RSV1, R131.1
unnamed: J113.RSV2, R132.1
unnamed: R133.2, U60.5
unnamed: D60.A, R135.1
unnamed: D59.C, R134.2
unnamed: D57.C, JP30.2
unnamed: C187.2, U62.1, Y16.P$2
unnamed: C188.1, U62.2, Y16.P$1
unnamed: D61.A, R139.1
unnamed: F16.1, J124.VBUS
unnamed: J121.RSV1, R140.1
unnamed: J121.RSV2, R141.1
unnamed: R142.2, U64.5
unnamed: D64.A, R144.1
unnamed: D63.C, R143.2
unnamed: D61.C, JP32.2
unnamed: C199.2, U66.1, Y17.P$2
unnamed: C200.1, U66.2, Y17.P$1
unnamed: D65.A, R148.1
unnamed: F17.1, J132.VBUS
unnamed: J129.RSV1, R149.1
unnamed: J129.RSV2, R150.1
unnamed: R151.2, U68.5
unnamed: D68.A, R153.1
unnamed: D67.C, R152.2
unnamed: D65.C, JP34.2
unnamed: C211.2, U70.1, Y18.P$2
unnamed: C212.1, U70.2, Y18.P$1
unnamed: D69.A, R157.1
unnamed: F18.1, J140.VBUS
unnamed: J137.RSV1, R158.1
unnamed: J137.RSV2, R159.1
unnamed: R160.2, U72.5
unnamed: D72.A, R162.1
unnamed: D71.C, R161.2
unnamed: D69.C, JP36.2
unnamed: C223.2, U74.1, Y19.P$2
unnamed: C224.1, U74.2, Y19.P$1
unnamed: D73.A, R166.1
unnamed: F19.1, J148.VBUS
unnamed: J145.RSV1, R167.1
unnamed: J145.RSV2, R168.1
unnamed: R169.2, U76.5
unnamed: D76.A, R171.1
unnamed: D75.C, R170.2
unnamed: D73.C, JP38.2
unnamed: C235.2, U78.1, Y20.P$2
unnamed: C236.1, U78.2, Y20.P$1
unnamed: D77.A, R175.1
unnamed: F20.1, J156.VBUS
unnamed: J153.RSV1, R176.1
unnamed: J153.RSV2, R177.1
unnamed: R178.2, U80.5
unnamed: D80.A, R180.1
unnamed: D79.C, R179.2
unnamed: D77.C, JP40.2
REGOUT: C6.1, U3.10
REGOUT1: C13.1, U5.10
REGOUT2: C25.1, U9.10
REGOUT3: C37.1, U13.10
REGOUT4: C49.1, U17.10
REGOUT5: C61.1, U21.10
REGOUT6: C73.1, U25.10
REGOUT7: C85.1, U29.10
REGOUT8: C97.1, U33.10
REGOUT9: C109.1, U37.10
REGOUT10: C121.1, U41.10
REGOUT11: C133.1, U45.10
REGOUT12: C145.1, U49.10
REGOUT13: C157.1, U53.10
REGOUT14: C169.1, U57.10
REGOUT15: C181.1, U61.10
REGOUT16: C193.1, U65.10
REGOUT17: C205.1, U69.10
REGOUT18: C217.1, U73.10
REGOUT19: C229.1, U77.10
SCL: J7.4, R2.1, U3.23, U4.32
SCL1: J11.4, R11.1, U5.23, U6.32
SCL2: J19.4, R20.1, U9.23, U10.32
SCL3: J27.4, R29.1, U13.23, U14.32
SCL4: J35.4, R38.1, U17.23, U18.32
SCL5: J43.4, R47.1, U21.23, U22.32
SCL6: J51.4, R56.1, U25.23, U26.32
SCL7: J59.4, R65.1, U29.23, U30.32
SCL8: J67.4, R74.1, U33.23, U34.32
SCL9: J75.4, R83.1, U37.23, U38.32
SCL10: J83.4, R92.1, U41.23, U42.32
SCL11: J91.4, R101.1, U45.23, U46.32
SCL12: J99.4, R110.1, U49.23, U50.32
SCL13: J107.4, R119.1, U53.23, U54.32
SCL14: J115.4, R128.1, U57.23, U58.32
SCL15: J123.4, R137.1, U61.23, U62.32
SCL16: J131.4, R146.1, U65.23, U66.32
SCL17: J139.4, R155.1, U69.23, U70.32
SCL18: J147.4, R164.1, U73.23, U74.32
SCL19: J155.4, R173.1, U77.23, U78.32
SDA: J7.3, R1.1, U3.24, U4.31
SDA1: J11.3, R10.1, U5.24, U6.31
SDA2: J19.3, R19.1, U9.24, U10.31
SDA3: J27.3, R28.1, U13.24, U14.31
SDA4: J35.3, R37.1, U17.24, U18.31
SDA5: J43.3, R46.1, U21.24, U22.31
SDA6: J51.3, R55.1, U25.24, U26.31
SDA7: J59.3, R64.1, U29.24, U30.31
SDA8: J67.3, R73.1, U33.24, U34.31
SDA9: J75.3, R82.1, U37.24, U38.31
SDA10: J83.3, R91.1, U41.24, U42.31
SDA11: J91.3, R100.1, U45.24, U46.31
SDA12: J99.3, R109.1, U49.24, U50.31
SDA13: J107.3, R118.1, U53.24, U54.31
SDA14: J115.3, R127.1, U57.24, U58.31
SDA15: J123.3, R136.1, U61.24, U62.31
SDA16: J131.3, R145.1, U65.24, U66.31
SDA17: J139.3, R154.1, U69.24, U70.31
SDA18: J147.3, R163.1, U73.24, U74.31
SDA19: J155.3, R172.1, U77.24, U78.31
SD_!CS!: J3.CS, U4.22
SD_!CS!1: J9.CS, U6.22
SD_!CS!2: J17.CS, U10.22
SD_!CS!3: J25.CS, U14.22
SD_!CS!4: J33.CS, U18.22
SD_!CS!5: J41.CS, U22.22
SD_!CS!6: J49.CS, U26.22
SD_!CS!7: J57.CS, U30.22
SD_!CS!8: J65.CS, U34.22
SD_!CS!9: J73.CS, U38.22
SD_!CS!10: J81.CS, U42.22
SD_!CS!11: J89.CS, U46.22
SD_!CS!12: J97.CS, U50.22
SD_!CS!13: J105.CS, U54.22
SD_!CS!14: J113.CS, U58.22
SD_!CS!15: J121.CS, U62.22
SD_!CS!16: J129.CS, U66.22
SD_!CS!17: J137.CS, U70.22
SD_!CS!18: J145.CS, U74.22
SD_!CS!19: J153.CS, U78.22
SD_MISO: J3.DO, U4.21
SD_MISO1: J9.DO, U6.21
SD_MISO2: J17.DO, U10.21
SD_MISO3: J25.DO, U14.21
SD_MISO4: J33.DO, U18.21
SD_MISO5: J41.DO, U22.21
SD_MISO6: J49.DO, U26.21
SD_MISO7: J57.DO, U30.21
SD_MISO8: J65.DO, U34.21
SD_MISO9: J73.DO, U38.21
SD_MISO10: J81.DO, U42.21
SD_MISO11: J89.DO, U46.21
SD_MISO12: J97.DO, U50.21
SD_MISO13: J105.DO, U54.21
SD_MISO14: J113.DO, U58.21
SD_MISO15: J121.DO, U62.21
SD_MISO16: J129.DO, U66.21
SD_MISO17: J137.DO, U70.21
SD_MISO18: J145.DO, U74.21
SD_MISO19: J153.DO, U78.21
SD_MOSI: J3.DI, U4.19
SD_MOSI1: J9.DI, U6.19
SD_MOSI2: J17.DI, U10.19
SD_MOSI3: J25.DI, U14.19
SD_MOSI4: J33.DI, U18.19
SD_MOSI5: J41.DI, U22.19
SD_MOSI6: J49.DI, U26.19
SD_MOSI7: J57.DI, U30.19
SD_MOSI8: J65.DI, U34.19
SD_MOSI9: J73.DI, U38.19
SD_MOSI10: J81.DI, U42.19
SD_MOSI11: J89.DI, U46.19
SD_MOSI12: J97.DI, U50.19
SD_MOSI13: J105.DI, U54.19
SD_MOSI14: J113.DI, U58.19
SD_MOSI15: J121.DI, U62.19
SD_MOSI16: J129.DI, U66.19
SD_MOSI17: J137.DI, U70.19
SD_MOSI18: J145.DI, U74.19
SD_MOSI19: J153.DI, U78.19
SD_SCK: J3.SCLK, U4.20
SD_SCK1: J9.SCLK, U6.20
SD_SCK2: J17.SCLK, U10.20
SD_SCK3: J25.SCLK, U14.20
SD_SCK4: J33.SCLK, U18.20
SD_SCK5: J41.SCLK, U22.20
SD_SCK6: J49.SCLK, U26.20
SD_SCK7: J57.SCLK, U30.20
SD_SCK8: J65.SCLK, U34.20
SD_SCK9: J73.SCLK, U38.20
SD_SCK10: J81.SCLK, U42.20
SD_SCK11: J89.SCLK, U46.20
SD_SCK12: J97.SCLK, U50.20
SD_SCK13: J105.SCLK, U54.20
SD_SCK14: J113.SCLK, U58.20
SD_SCK15: J121.SCLK, U62.20
SD_SCK16: J129.SCLK, U66.20
SD_SCK17: J137.SCLK, U70.20
SD_SCK18: J145.SCLK, U74.20
SD_SCK19: J153.SCLK, U78.20
SHIELD: J2.SHIELD1, J2.SHIELD2, J2.SHIELD3
SHIELD1: J12.SHIELD1, J12.SHIELD2, J12.SHIELD3
SHIELD2: J20.SHIELD1, J20.SHIELD2, J20.SHIELD3
SHIELD3: J28.SHIELD1, J28.SHIELD2, J28.SHIELD3
SHIELD4: J36.SHIELD1, J36.SHIELD2, J36.SHIELD3
SHIELD5: J44.SHIELD1, J44.SHIELD2, J44.SHIELD3
SHIELD6: J52.SHIELD1, J52.SHIELD2, J52.SHIELD3
SHIELD7: J60.SHIELD1, J60.SHIELD2, J60.SHIELD3
SHIELD8: J68.SHIELD1, J68.SHIELD2, J68.SHIELD3
SHIELD9: J76.SHIELD1, J76.SHIELD2, J76.SHIELD3
SHIELD10: J84.SHIELD1, J84.SHIELD2, J84.SHIELD3
SHIELD11: J92.SHIELD1, J92.SHIELD2, J92.SHIELD3
SHIELD12: J100.SHIELD1, J100.SHIELD2, J100.SHIELD3
SHIELD13: J108.SHIELD1, J108.SHIELD2, J108.SHIELD3
SHIELD14: J116.SHIELD1, J116.SHIELD2, J116.SHIELD3
SHIELD15: J124.SHIELD1, J124.SHIELD2, J124.SHIELD3
SHIELD16: J132.SHIELD1, J132.SHIELD2, J132.SHIELD3
SHIELD17: J140.SHIELD1, J140.SHIELD2, J140.SHIELD3
SHIELD18: J148.SHIELD1, J148.SHIELD2, J148.SHIELD3
SHIELD19: J156.SHIELD1, J156.SHIELD2, J156.SHIELD3
SWCLK: JP3.4, TP1.P$1, U4.45
SWCLK1: JP2.4, TP3.P$1, U6.45
SWCLK2: JP5.4, TP5.P$1, U10.45
SWCLK3: JP7.4, TP7.P$1, U14.45
SWCLK4: JP9.4, TP9.P$1, U18.45
SWCLK5: JP11.4, TP11.P$1, U22.45
SWCLK6: JP13.4, TP13.P$1, U26.45
SWCLK7: JP15.4, TP15.P$1, U30.45
SWCLK8: JP17.4, TP17.P$1, U34.45
SWCLK9: JP19.4, TP19.P$1, U38.45
SWCLK10: JP21.4, TP21.P$1, U42.45
SWCLK11: JP23.4, TP23.P$1, U46.45
SWCLK12: JP25.4, TP25.P$1, U50.45
SWCLK13: JP27.4, TP27.P$1, U54.45
SWCLK14: JP29.4, TP29.P$1, U58.45
SWCLK15: JP31.4, TP31.P$1, U62.45
SWCLK16: JP33.4, TP33.P$1, U66.45
SWCLK17: JP35.4, TP35.P$1, U70.45
SWCLK18: JP37.4, TP37.P$1, U74.45
SWCLK19: JP39.4, TP39.P$1, U78.45
SWDIO: JP3.2, TP2.P$1, U4.46
SWDIO1: JP2.2, TP4.P$1, U6.46
SWDIO2: JP5.2, TP6.P$1, U10.46
SWDIO3: JP7.2, TP8.P$1, U14.46
SWDIO4: JP9.2, TP10.P$1, U18.46
SWDIO5: JP11.2, TP12.P$1, U22.46
SWDIO6: JP13.2, TP14.P$1, U26.46
SWDIO7: JP15.2, TP16.P$1, U30.46
SWDIO8: JP17.2, TP18.P$1, U34.46
SWDIO9: JP19.2, TP20.P$1, U38.46
SWDIO10: JP21.2, TP22.P$1, U42.46
SWDIO11: JP23.2, TP24.P$1, U46.46
SWDIO12: JP25.2, TP26.P$1, U50.46
SWDIO13: JP27.2, TP28.P$1, U54.46
SWDIO14: JP29.2, TP30.P$1, U58.46
SWDIO15: JP31.2, TP32.P$1, U62.46
SWDIO16: JP33.2, TP34.P$1, U66.46
SWDIO17: JP35.2, TP36.P$1, U70.46
SWDIO18: JP37.2, TP38.P$1, U74.46
SWDIO19: JP39.2, TP40.P$1, U78.46
VDDCORE: C9.1, U4.43
VDDCORE1: C16.1, U6.43
VDDCORE2: C28.1, U10.43
VDDCORE3: C40.1, U14.43
VDDCORE4: C52.1, U18.43
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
